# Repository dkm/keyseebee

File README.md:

# PouetPouet

The firmware is [Keyberon](https://github.com/TeXitoi/keyberon), a
pure rust firmware.

## Features

 * 60 keys, using Cherry MX switches, only 1U keycaps;
 * USB-C connector;
 * 1 STM32F072 MCU, with hardware USB DFU bootloader and crystal less USB;
 * Only onboard SMD component (except for the switches).

## Inspiration

 * [Keyseebee](https://github.com/TeXitoi/keyseebee) for being the «I will change it quickly and have something ready in an hour» base project (even if I ended up redoing most of the hardware design).
 * [Steamvan](https://github.com/jmdaly/steamvan) for some KiCad design ideas;
 * [help-14](https://github.com/help-14/mechanical-keyboard) for making a nice list of existing keyboard;
 * [Masterzen](http://www.masterzen.fr/2020/05/03/designing-a-keyboard-part-1/) and many others for writing online tutorials for newbies like me.

## Bill Of Materials

|Item                                                                      |Package|Qty|Remarks                                |Price |
|--------------------------------------------------------------------------|-------|--:|---------------------------------------|-----:|

## Compiling and flashing

Install the complete toolchain and utils:

```shell
curl https://sh.rustup.rs -sSf | sh
rustup target add thumbv6m-none-eabi
rustup component add llvm-tools-preview
cargo install cargo-binutils
sudo apt-get install dfu-util
```

Compile:

```shell
cd firmware
cargo objcopy --bin pouetpouet --release -- -O binary pouetpouet.bin
```

To flash using dfu-util, first put the board in dfu mode by pressing
BOOT, pressing and releasing RESET and releasing BOOT. Then:

```shell
dfu-util -d 0483:df11 -a 0 -s 0x08000000:leave -D pouetpouet.bin
```

The fist time, if the write fail, your flash might be protected. To
unprotect:

```shell
dfu-util -d 0483:df11 -a 0 -s 0x08000000:force:unprotect -D pouetpouet.bin
```

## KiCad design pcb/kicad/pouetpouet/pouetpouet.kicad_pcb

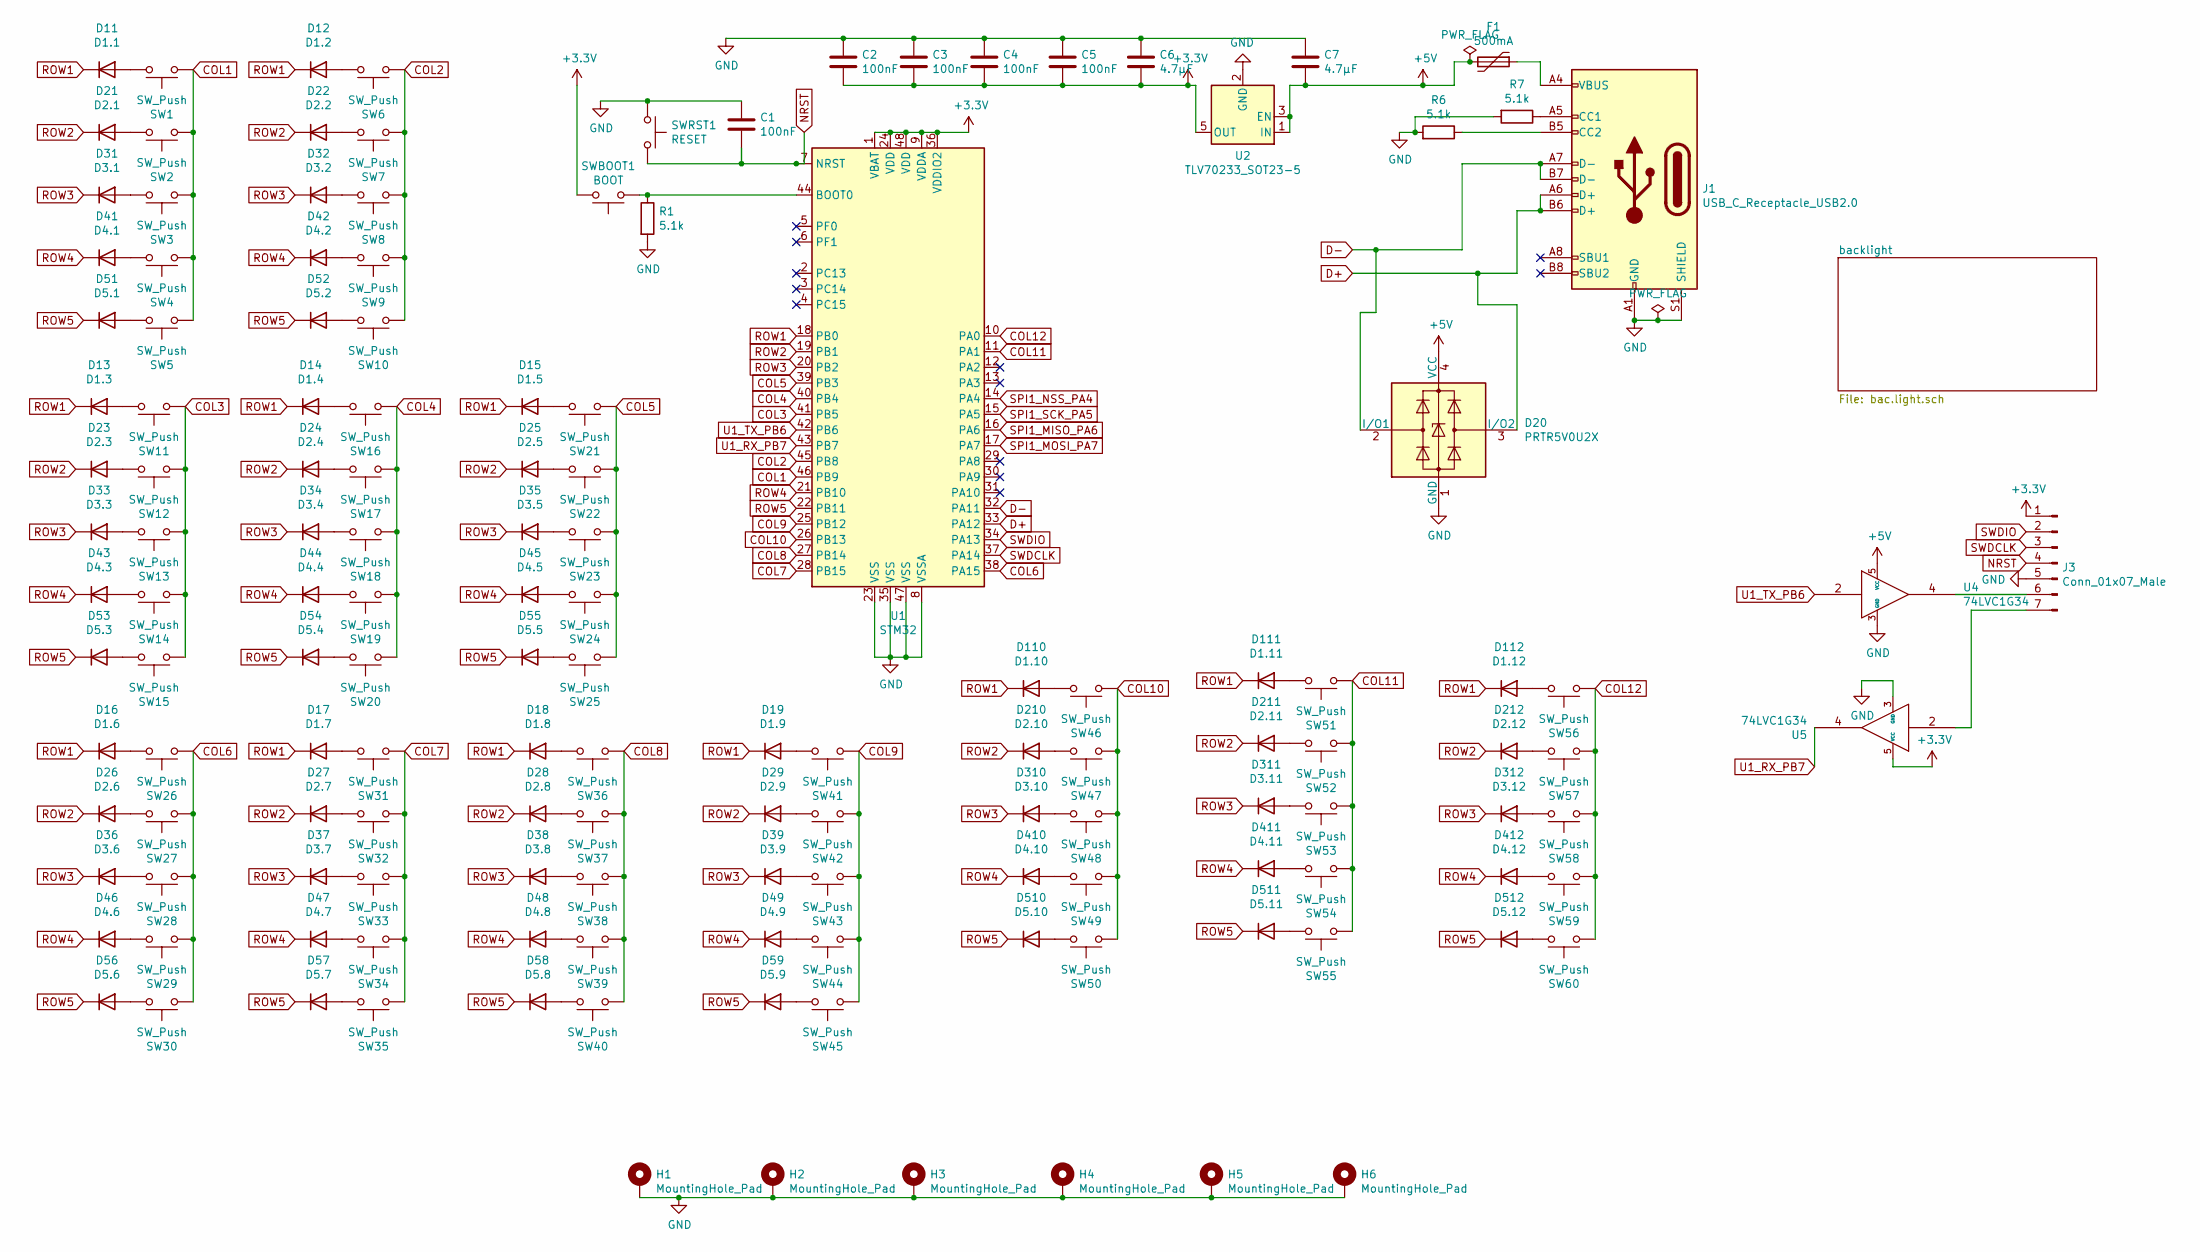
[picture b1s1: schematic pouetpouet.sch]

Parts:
C1, C2, C3, C4, C5: 100nF; C_0805_2012Metric_Pad1.15x1.40mm_HandSolder
C6, C7: 4.7µF; C_0805_2012Metric_Pad1.15x1.40mm_HandSolder
D11: D1.1; D_SOD-323
D12: D1.2; D_SOD-323
D13: D1.3; D_SOD-323
D14: D1.4; D_SOD-323
D15: D1.5; D_SOD-323
D16: D1.6; D_SOD-323
D17: D1.7; D_SOD-323
D18: D1.8; D_SOD-323
D19: D1.9; D_SOD-323
D20: PRTR5V0U2X; SOT-143
D21: D2.1; D_SOD-323
D22: D2.2; D_SOD-323
D23: D2.3; D_SOD-323
D24: D2.4; D_SOD-323
D25: D2.5; D_SOD-323
D26: D2.6; D_SOD-323
D27: D2.7; D_SOD-323
D28: D2.8; D_SOD-323
D29: D2.9; D_SOD-323
D31: D3.1; D_SOD-323
D32: D3.2; D_SOD-323
D33: D3.3; D_SOD-323
D34: D3.4; D_SOD-323
D35: D3.5; D_SOD-323
D36: D3.6; D_SOD-323
D37: D3.7; D_SOD-323
D38: D3.8; D_SOD-323
D39: D3.9; D_SOD-323
D41: D4.1; D_SOD-323
D42: D4.2; D_SOD-323
D43: D4.3; D_SOD-323
D44: D4.4; D_SOD-323
D45: D4.5; D_SOD-323
D46: D4.6; D_SOD-323
D47: D4.7; D_SOD-323
D48: D4.8; D_SOD-323
D49: D4.9; D_SOD-323
D51: D5.1; D_SOD-323
D52: D5.2; D_SOD-323
D53: D5.3; D_SOD-323
D54: D5.4; D_SOD-323
D55: D5.5; D_SOD-323
D56: D5.6; D_SOD-323
D57: D5.7; D_SOD-323
D58: D5.8; D_SOD-323
D59: D5.9; D_SOD-323
D110: D1.10; D_SOD-323
D111: D1.11; D_SOD-323
D112: D1.12; D_SOD-323
D210: D2.10; D_SOD-323
D211: D2.11; D_SOD-323
D212: D2.12; D_SOD-323
D310: D3.10; D_SOD-323
D311: D3.11; D_SOD-323
D312: D3.12; D_SOD-323
D410: D4.10; D_SOD-323
D411: D4.11; D_SOD-323
D412: D4.12; D_SOD-323
D510: D5.10; D_SOD-323
D511: D5.11; D_SOD-323
D512: D5.12; D_SOD-323
F1: 500mA; R_0805_2012Metric_Pad1.15x1.40mm_HandSolder
H1, H2, H3, H4, H5, H6: MountingHole_Pad; MountingHole_2.2mm_M2_Pad
J1: USB_C_Receptacle_USB2.0; USB_C_Receptacle_HRO_TYPE-C-31-M-12
J3: Conn_01x07_Male; Harwin_M20-89007xx_1x07_P2.54mm_Horizontal
R1, R6, R7: 5.1k; R_0805_2012Metric_Pad1.15x1.40mm_HandSolder
SW1, SW2, SW3, SW4, SW5, SW6, SW7, SW8, SW9, SW10, SW11, SW12, SW13, SW14, SW15, SW16, SW17, SW18, SW19, SW20, SW21, SW22, SW23, SW24, SW25, SW26, SW27, SW28, SW29, SW30, SW31, SW32, SW33, SW34, SW35, SW36, SW37, SW38, SW39, SW40, SW41, SW42, SW43, SW44, SW45, SW46, SW47, SW48, SW49, SW50, SW51, SW52, SW53, SW54, SW55, SW56, SW57, SW58, SW59, SW60: SW_Push; SW_Cherry_MX_1.00u_PCB
SWBOOT1: BOOT; SW_SPST_CK_RS282G05A3
SWRST1: RESET; SW_SPST_CK_RS282G05A3
U1: STM32; LQFP-48_7x7mm_P0.5mm
U2: TLV70233_SOT23-5; SOT-23-5
U4, U5: 74LVC1G34; SOT-353_SC-70-5

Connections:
+3V3: C2.2, C3.2, C4.2, C5.2, C6.2, J3.1, SWBOOT1.2, U1.1 (VBAT), U1.9 (VDDA), U1.24 (VDD), U1.36 (VDDIO2), U1.48 (VDD), U2.5 (OUT), U5.5 (VCC)
+5V: C7.2, D20.4 (VCC), F1.2, U2.1 (IN), U2.3 (EN), U4.5 (VCC); also elsewhere on the board
COL1: SW1.1, SW2.1, SW3.1, SW4.1, SW5.1, U1.46 (PB9)
COL2: SW6.1, SW7.1, SW8.1, SW9.1, SW10.1, U1.45 (PB8)
COL3: SW11.1, SW12.1, SW13.1, SW14.1, SW15.1, U1.41 (PB5)
COL4: SW16.1, SW17.1, SW18.1, SW19.1, SW20.1, U1.40 (PB4)
COL5: SW21.1, SW22.1, SW23.1, SW24.1, SW25.1, U1.39 (PB3)
COL6: SW26.1, SW27.1, SW28.1, SW29.1, SW30.1, U1.38 (PA15)
COL7: SW31.1, SW32.1, SW33.1, SW34.1, SW35.1, U1.28 (PB15)
COL8: SW36.1, SW37.1, SW38.1, SW39.1, SW40.1, U1.27 (PB14)
COL9: SW41.1, SW42.1, SW43.1, SW44.1, SW45.1, U1.25 (PB12)
COL10: SW46.1, SW47.1, SW48.1, SW49.1, SW50.1, U1.26 (PB13)
COL11: SW51.1, SW52.1, SW53.1, SW54.1, SW55.1, U1.11 (PA1)
COL12: SW56.1, SW57.1, SW58.1, SW59.1, SW60.1, U1.10 (PA0)
D+: D20.3 (I/O2), J1.A6 (D+), J1.B6 (D+), U1.33 (PA12)
D-: D20.2 (I/O1), J1.A7 (D-), J1.B7 (D-), U1.32 (PA11)
GND: C1.1, C2.1, C3.1, C4.1, C5.1, C6.1, C7.1, D20.1 (GND), H1.1, H2.1, H3.1, H4.1, H5.1, H6.1, J1.A1 (GND), J1.A12 (GND), J1.B1 (GND), J1.B12 (GND), J1.S1 (SHIELD), J3.5, R1.2, R6.2, R7.2, SWRST1.1, U1.8 (VSSA), U1.23 (VSS), U1.35 (VSS), U1.47 (VSS), U2.2 (GND), U4.3 (GND), U5.3 (GND); also elsewhere on the board
NRST: C1.2, J3.4, SWRST1.2, U1.7 (NRST)
unnamed: D11.2 (A), SW1.2
unnamed: D12.2 (A), SW6.2
unnamed: D13.2 (A), SW11.2
unnamed: D14.2 (A), SW16.2
unnamed: D15.2 (A), SW21.2
unnamed: D16.2 (A), SW26.2
unnamed: D17.2 (A), SW31.2
unnamed: D18.2 (A), SW36.2
unnamed: D19.2 (A), SW41.2
unnamed: D21.2 (A), SW2.2
unnamed: D22.2 (A), SW7.2
unnamed: D23.2 (A), SW12.2
unnamed: D24.2 (A), SW17.2
unnamed: D25.2 (A), SW22.2
unnamed: D26.2 (A), SW27.2
unnamed: D27.2 (A), SW32.2
unnamed: D28.2 (A), SW37.2
unnamed: D29.2 (A), SW42.2
unnamed: D31.2 (A), SW3.2
unnamed: D32.2 (A), SW8.2
unnamed: D33.2 (A), SW13.2
unnamed: D34.2 (A), SW18.2
unnamed: D35.2 (A), SW23.2
unnamed: D36.2 (A), SW28.2
unnamed: D37.2 (A), SW33.2
unnamed: D38.2 (A), SW38.2
unnamed: D39.2 (A), SW43.2
unnamed: D41.2 (A), SW4.2
unnamed: D42.2 (A), SW9.2
unnamed: D43.2 (A), SW14.2
unnamed: D44.2 (A), SW19.2
unnamed: D45.2 (A), SW24.2
unnamed: D46.2 (A), SW29.2
unnamed: D47.2 (A), SW34.2
unnamed: D48.2 (A), SW39.2
unnamed: D49.2 (A), SW44.2
unnamed: D51.2 (A), SW5.2
unnamed: D52.2 (A), SW10.2
unnamed: D53.2 (A), SW15.2
unnamed: D54.2 (A), SW20.2
unnamed: D55.2 (A), SW25.2
unnamed: D56.2 (A), SW30.2
unnamed: D57.2 (A), SW35.2
unnamed: D58.2 (A), SW40.2
unnamed: D59.2 (A), SW45.2
unnamed: D110.2 (A), SW46.2
unnamed: D111.2 (A), SW51.2
unnamed: D112.2 (A), SW56.2
unnamed: D210.2 (A), SW47.2
unnamed: D211.2 (A), SW52.2
unnamed: D212.2 (A), SW57.2
unnamed: D310.2 (A), SW48.2
unnamed: D311.2 (A), SW53.2
unnamed: D312.2 (A), SW58.2
unnamed: D410.2 (A), SW49.2
unnamed: D411.2 (A), SW54.2
unnamed: D412.2 (A), SW59.2
unnamed: D510.2 (A), SW50.2
unnamed: D511.2 (A), SW55.2
unnamed: D512.2 (A), SW60.2
unnamed: F1.1, J1.A4 (VBUS), J1.A9 (VBUS), J1.B4 (VBUS), J1.B9 (VBUS)
unnamed: J1.A5 (CC1), R7.1
unnamed: J1.B5 (CC2), R6.1
unnamed: J3.6, U4.4
unnamed: J3.7, U5.2
unnamed: R1.1, SWBOOT1.1, U1.44 (BOOT0)
ROW1: D11.1 (K), D12.1 (K), D13.1 (K), D14.1 (K), D15.1 (K), D16.1 (K), D17.1 (K), D18.1 (K), D19.1 (K), D110.1 (K), D111.1 (K), D112.1 (K), U1.18 (PB0)
ROW2: D21.1 (K), D22.1 (K), D23.1 (K), D24.1 (K), D25.1 (K), D26.1 (K), D27.1 (K), D28.1 (K), D29.1 (K), D210.1 (K), D211.1 (K), D212.1 (K), U1.19 (PB1)
ROW3: D31.1 (K), D32.1 (K), D33.1 (K), D34.1 (K), D35.1 (K), D36.1 (K), D37.1 (K), D38.1 (K), D39.1 (K), D310.1 (K), D311.1 (K), D312.1 (K), U1.20 (PB2)
ROW4: D41.1 (K), D42.1 (K), D43.1 (K), D44.1 (K), D45.1 (K), D46.1 (K), D47.1 (K), D48.1 (K), D49.1 (K), D410.1 (K), D411.1 (K), D412.1 (K), U1.21 (PB10)
ROW5: D51.1 (K), D52.1 (K), D53.1 (K), D54.1 (K), D55.1 (K), D56.1 (K), D57.1 (K), D58.1 (K), D59.1 (K), D510.1 (K), D511.1 (K), D512.1 (K), U1.22 (PB11)
SPI1_MOSI_PA7: U1.17 (PA7); also elsewhere on the board
SWDCLK: J3.3, U1.37 (PA14)
SWDIO: J3.2, U1.34 (PA13)
U1_RX_PB7: U1.43 (PB7), U5.4
U1_TX_PB6: U1.42 (PB6), U4.2

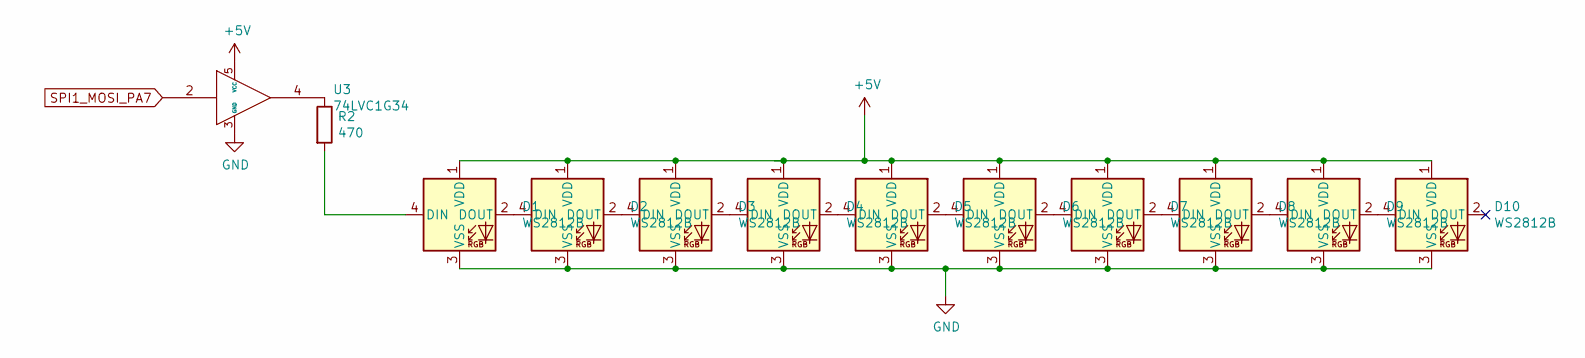
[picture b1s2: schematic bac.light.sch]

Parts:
D1, D2, D3, D4, D5, D6, D7, D8, D9, D10: WS2812B; LED_WS2812B_PLCC4_5.0x5.0mm_P3.2mm
R2: 470; R_0805_2012Metric_Pad1.15x1.40mm_HandSolder
U3: 74LVC1G34; SOT-353_SC-70-5

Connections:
+5V: D1.1 (VDD), D2.1 (VDD), D3.1 (VDD), D4.1 (VDD), D5.1 (VDD), D6.1 (VDD), D7.1 (VDD), D8.1 (VDD), D9.1 (VDD), D10.1 (VDD), U3.5 (VCC); also elsewhere on the board
GND: D1.3 (VSS), D2.3 (VSS), D3.3 (VSS), D4.3 (VSS), D5.3 (VSS), D6.3 (VSS), D7.3 (VSS), D8.3 (VSS), D9.3 (VSS), D10.3 (VSS), U3.3 (GND); also elsewhere on the board
unnamed: D1.2 (DOUT), D2.4 (DIN)
unnamed: D1.4 (DIN), R2.2
unnamed: D2.2 (DOUT), D3.4 (DIN)
unnamed: D3.2 (DOUT), D4.4 (DIN)
unnamed: D4.2 (DOUT), D5.4 (DIN)
unnamed: D5.2 (DOUT), D6.4 (DIN)
unnamed: D6.2 (DOUT), D7.4 (DIN)
unnamed: D7.2 (DOUT), D8.4 (DIN)
unnamed: D8.2 (DOUT), D9.4 (DIN)
unnamed: D9.2 (DOUT), D10.4 (DIN)
unnamed: R2.1, U3.4
SPI1_MOSI_PA7: U3.2; also elsewhere on the board

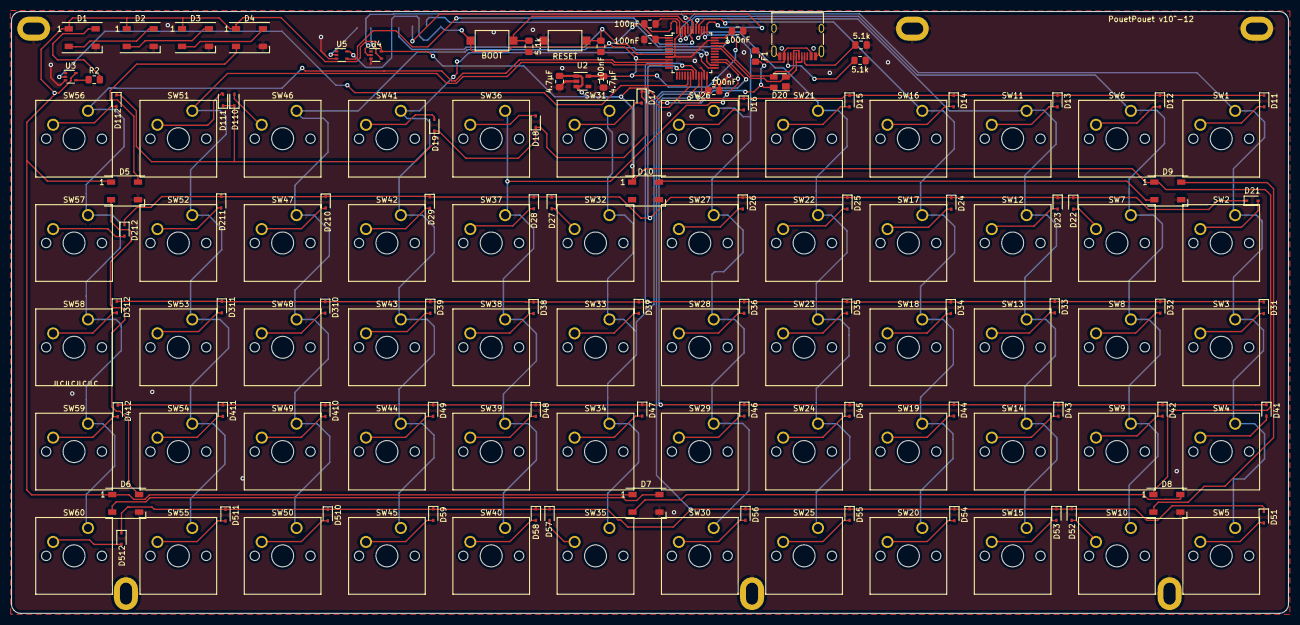
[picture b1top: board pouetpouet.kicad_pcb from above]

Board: 2 copper layers, 232.6 x 109.6 mm, 158 parts (1 on the bottom side), 105 nets.

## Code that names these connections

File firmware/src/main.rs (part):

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    stm32::SPI1,
    gpioa::PA5<Alternate<AF0>>,
    gpioa::PA6<Alternate<AF0>>,
    gpioa::PA7<Alternate<AF0>>,
    EightBit,
>;

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}

pub struct Cols(
    gpioa::PA0<Input<PullUp>>,  // 12
    gpioa::PA1<Input<PullUp>>,  // 11
    gpiob::PB13<Input<PullUp>>, // 10
    gpiob::PB12<Input<PullUp>>, // 9
    gpiob::PB14<Input<PullUp>>, // 8
    gpiob::PB15<Input<PullUp>>, // 7
    gpioa::PA15<Input<PullUp>>, // 6
    gpiob::PB3<Input<PullUp>>,  // 5
    gpiob::PB4<Input<PullUp>>,  // 4
    gpiob::PB5<Input<PullUp>>,  // 3
    gpiob::PB8<Input<PullUp>>,  // 2
    gpiob::PB9<Input<PullUp>>,  // 1
);
impl_heterogenous_array! {
    Cols,
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}

pub struct Rows(
    gpiob::PB0<Output<PushPull>>,
    gpiob::PB1<Output<PushPull>>,
    gpiob::PB2<Output<PushPull>>,
    gpiob::PB10<Output<PushPull>>,
    gpiob::PB11<Output<PushPull>>,
);
impl_heterogenous_array! {
    Rows,
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
        let usb = usb::Peripheral {
            usb: c.device.USB,
            pin_dm: gpioa.pa11,
            pin_dp: gpioa.pa12,
        };
        *USB_BUS = Some(usb::UsbBusType::new(usb));
        let usb_bus = USB_BUS.as_ref().unwrap();
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
        let pa5 = gpioa.pa5; // sck
        let pa6 = gpioa.pa6; // miso
        let pa7 = gpioa.pa7; // mosi

        // Configure pins for SPI
        let (sck, miso, mosi) = cortex_m::interrupt::free(move |cs| {
            (
                pa5.into_alternate_af0(cs),
                pa6.into_alternate_af0(cs),
                pa7.into_alternate_af0(cs),
            )
        });

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        let mut timer = timers::Timer::tim3(c.device.TIM3, 1.khz(), &mut rcc);
        timer.listen(timers::Event::TimeOut);

        let pa15 = gpioa.pa15;
        let pa1 = gpioa.pa1;
        let pa0 = gpioa.pa0;

        let matrix = cortex_m::interrupt::free(move |cs| {
            Matrix::new(
                Cols(
                    pa0.into_pull_up_input(cs),
                    pa1.into_pull_up_input(cs),
                    gpiob.pb13.into_pull_up_input(cs),
                    gpiob.pb12.into_pull_up_input(cs),
                    gpiob.pb14.into_pull_up_input(cs),
                    gpiob.pb15.into_pull_up_input(cs),
                    pa15.into_pull_up_input(cs),
                    gpiob.pb3.into_pull_up_input(cs),
                    gpiob.pb4.into_pull_up_input(cs),
                    gpiob.pb5.into_pull_up_input(cs),
                    gpiob.pb8.into_pull_up_input(cs),
                    gpiob.pb9.into_pull_up_input(cs),
                ),
                Rows(
                    gpiob.pb0.into_push_pull_output(cs),
                    gpiob.pb1.into_push_pull_output(cs),
                    gpiob.pb2.into_push_pull_output(cs),
                    gpiob.pb10.into_push_pull_output(cs),
                    gpiob.pb11.into_push_pull_output(cs),
                ),
            )
        });
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
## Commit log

2020-09-02 WIP for ortho 12x5
2020-09-03 WIP add lib
2020-09-06 WIP: some more routing
2020-09-06 fix footprind wrt silk
2020-09-07 WIP routing
2020-09-09 WIP: routing, changed visual layout of diodes
    let go of nice diode array, too hard to route
2020-09-09 WIP DRC and unconnected sw
2020-09-09 WIP: routing complete
2020-09-11 WIP: use more std footprint for MX only
    - reverse switch to match footprint
    - correct all DRC issues
    - simplify some routes.
2020-09-17 wip
    change footprint for debug pins, MCU, correctly route WS2812
2020-09-23 change LDO, add filter on USB, move capacitors
2020-09-24 WIP.
    add buffer for rx/tx pad to level up the signal from 3.3 to 5.
2020-09-25 move capacitor for all VDDs
2020-09-26 change ESD part, better handling mounting hole, remove unused pin on debug connector
2020-09-27 fix buffer for RX pin
2020-09-28 wip: update readme, fix ERC errors
2020-12-22 WIP: backlight in progress
2021-01-03 WIP: backlight
2021-01-03 Allow for minor version change in dependencies
